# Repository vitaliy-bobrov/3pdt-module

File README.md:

# 3PDT footswitch + brightness trimmer PCB

3PDT footswitch, LED and brightness trimmer module PCB KiCad files.

The repository contains KiCad source files: schematic, PCB.

## Schematic

## PCB (3D preview)

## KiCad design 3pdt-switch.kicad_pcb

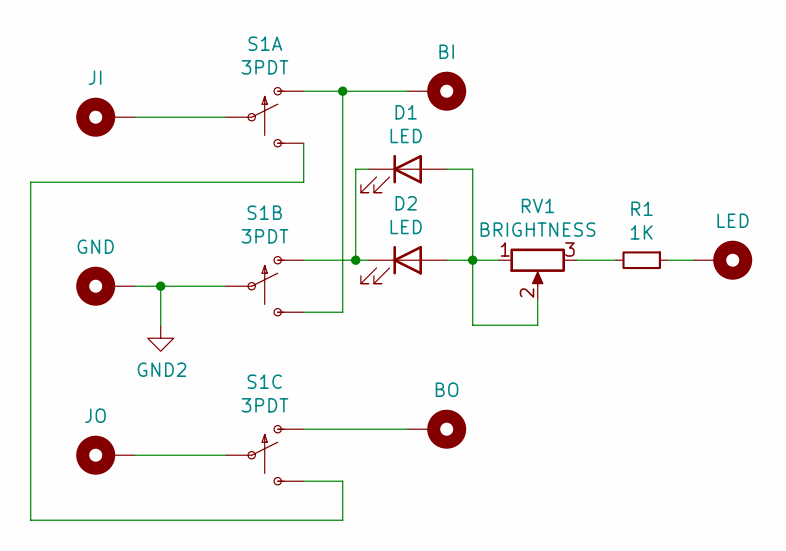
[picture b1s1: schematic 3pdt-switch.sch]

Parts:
D1, D2: LED; 3MM_IO
H1: BI; PAD1
H2: JI; PAD1
H3: LED; PAD1
H4: GND; PAD1
H5: BO; PAD1
H6: JO; PAD1
R1: 1K; 0.3_22.B
RV1: BRIGHTNESS; TRIM1
S1: 3PDT; 3PDT.LUGS.SPF

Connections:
GND2: H4.1, S1.P$5
unnamed: D1.1 (K), D2.1 (K), S1.P$4 (O)
unnamed: D1.2 (A), D2.2 (A), RV1.1, RV1.2
unnamed: H1.1, S1.P$1 (O), S1.P$6 (S)
unnamed: H2.1, S1.P$2
unnamed: H3.1, R1.1
unnamed: H5.1, S1.P$7 (O)
unnamed: H6.1, S1.P$8
unnamed: R1.2, RV1.3
unnamed: S1.P$3 (S), S1.P$9 (S)

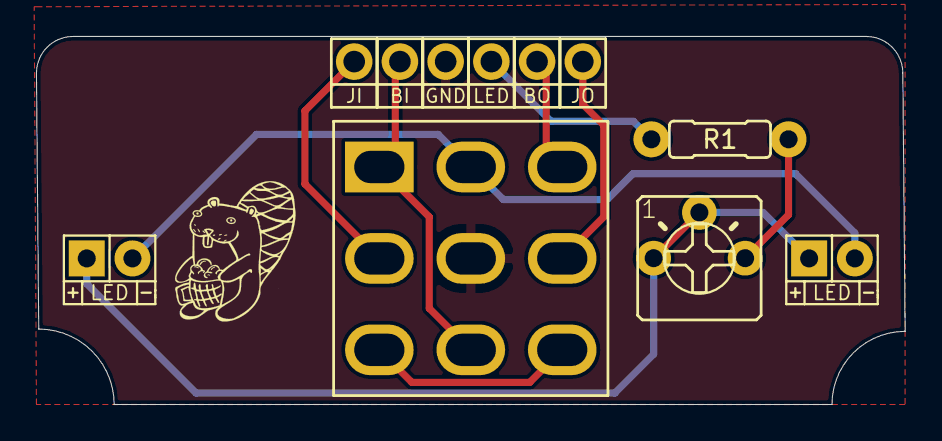
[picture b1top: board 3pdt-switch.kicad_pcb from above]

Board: 2 copper layers, 48.3 x 20.4 mm, 11 parts (0 on the bottom side), 10 nets.

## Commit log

2021-07-30 v1.1
